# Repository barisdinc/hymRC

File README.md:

Bu projenin amaci role olarak kullanilmak uzere hazirlanan duzeneklerin kontrolunu saglamak ve bu sistemin uzaktan kumandasi ile tanitim bilgilerini olusturacak bir kart tasarimi yapmaktir.

Bu proje **_TA7OM Hudaverdi Gunes_**'in tesviki ile baslatilmistir. Mevcutta yillar once yaptigimiz ve pek cok rolede kullanilan genelde PIC tabanli Role Kontrol kartlarinin daha modern hale getirilmesi hedeflenecektir.

Aklimizdaki ozellikler asagidaki gibidir;

### Temel Ozellikler
1. Islemci unitesi olarak PIC yerine kolay erisilebilir ve programlanabilir ATMEL (Arduino) tercih edilecektir
1. 12 Volt ile beslenecektir
1. Role kontrol ozellikleri olacaktir
1. Durum gosterimi icin LED bulunacaktir
1. Dis arayuz baglantilari optokupler veya roleler uzerinden yapilacaktir
1. COR/CAS destegi olmalidir
1. COR/CAS destegi +/- olabilmelidir
1. Ayarlarin gosterimi icin LCD bulunacaktir (opsiyonel)
1. Ayarlarin goruntulenmesi/degistirilmesi icin rotary encoder bulunacaktir (opsiyonel)
1. Sistem icinde gercek zaman saati bulunacaktir (opsiyonel)
1. Roleye simplex Link sistemi ilave edilebilmelidir
  * Link COR girişi olmalı
  * Ancak Link girişinden sinyal geldiğinde Role de Kuyruk süresi olmamalı
  * İki VHF cihaz ile yapılan Role bir birine UHF üzerinden ücüncü cihaz ile Linkli olsun. 
  * iki cihazdan yapılan VHF Role Normal aktivtesini sürdürürken Kullanıcı Mandalı attığında Role göndermede iken aynı zamanda UHF link cihazı da göndermeye geçmelidir. 
  * Kullanıcı Mandalı bıraktığında Role Kuruk süresi sonrasında kapanacak ancak Link ise hiçbir gecikme olmadan, yani kuyruk süresi olmadan anında kapanacak. Bunun amacı Link üzerinden gelen sinyal zaten bir rokleden gelmekte olup, üzerinde kuyruk süresi vardır. 
  * ikinci bir kuyruk süresine ihtiyaç yoktur.
1. ...

### Role KOntrol Ozellikleri
1. Squelch/Sinyal girisi
1. Otomatik enterferans engelleme
1. ... 

### Uzaktan Kumanda Ozellikleri
1. DTMF ile uzaktan kumanda ozelligi olacaktir
1. Role acma/kapatma
1. Ton acma/kapatma
1. Morse tanitim acma/kapatma
1. AX25 tanitim acma/kapatma
1. belirlenen sure boyunca kapali kalma
1. Otomatik enterferans engelleme acma/kapama
1. Link acma/kapama
1. Kuyruk suresi ayari (uzun/orta/kisa)
1. Fan/Role acma/kapatma
1. AX25 ile uzaktan ayar yuklenmesi yapilabilecektir (opsiyonel)
1. SSTV Goruntusu iste (opsiyonel)
1. ...

### Tanitim Bilgisi
1. Beacon Tanitim ozelligi bulunacaktir (Orn: YM7KO 88.5 KN80WU 5W -10C 138V 121220 1919)
  * Morse olarak istasyon tanitimi basacaktir
  * Morse tanitim icinde asagidaki bilgiler olacaktir
  * Ton bilgisi
  * Lokasyon bilgisi (grid   square)
  * Cikis Gucu
  * Ortam sicakligi
  * Aku voltajlari
  * Tarih ve saat (gercek zamani opsiyonu durumunda
  * ...
  
1. Uzaktan kumanda sifre kontrollu olacaktir
  * Sifre uzaktan degistirilebilecektir
  * Sifre tanimli bir sifre kumesinden (Orn: 10 degisik sifre) sirayla degisecektir, aktif sifre no sorgulanabilecektir
  * ...
  
1. Beacon sinyali AX25 olarak da gonderilecektir
  * AX25 beacon sinyali icinde rolenin tum ayarlarinin aktif durumu bulunabilecektir
  * ...

**NOT:** Liste ilgili goruslerinizi ve eklenmesini istediginiz ozellikleri ISSUE bolumunden veya email ile bize bildiriniz. (barisdinc###gmail.com)

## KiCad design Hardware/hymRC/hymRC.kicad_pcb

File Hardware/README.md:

This folder will contain Schematic and PCB versions for different repeater application options

PCBs arrived...
<IMG SRC=https://github.com/barisdinc/hymRC/blob/main/Hardware/HYMRC_pcb1.jpeg>
<IMG SRC=https://github.com/barisdinc/hymRC/blob/main/Hardware/HYMRC_pcb2.jpeg>

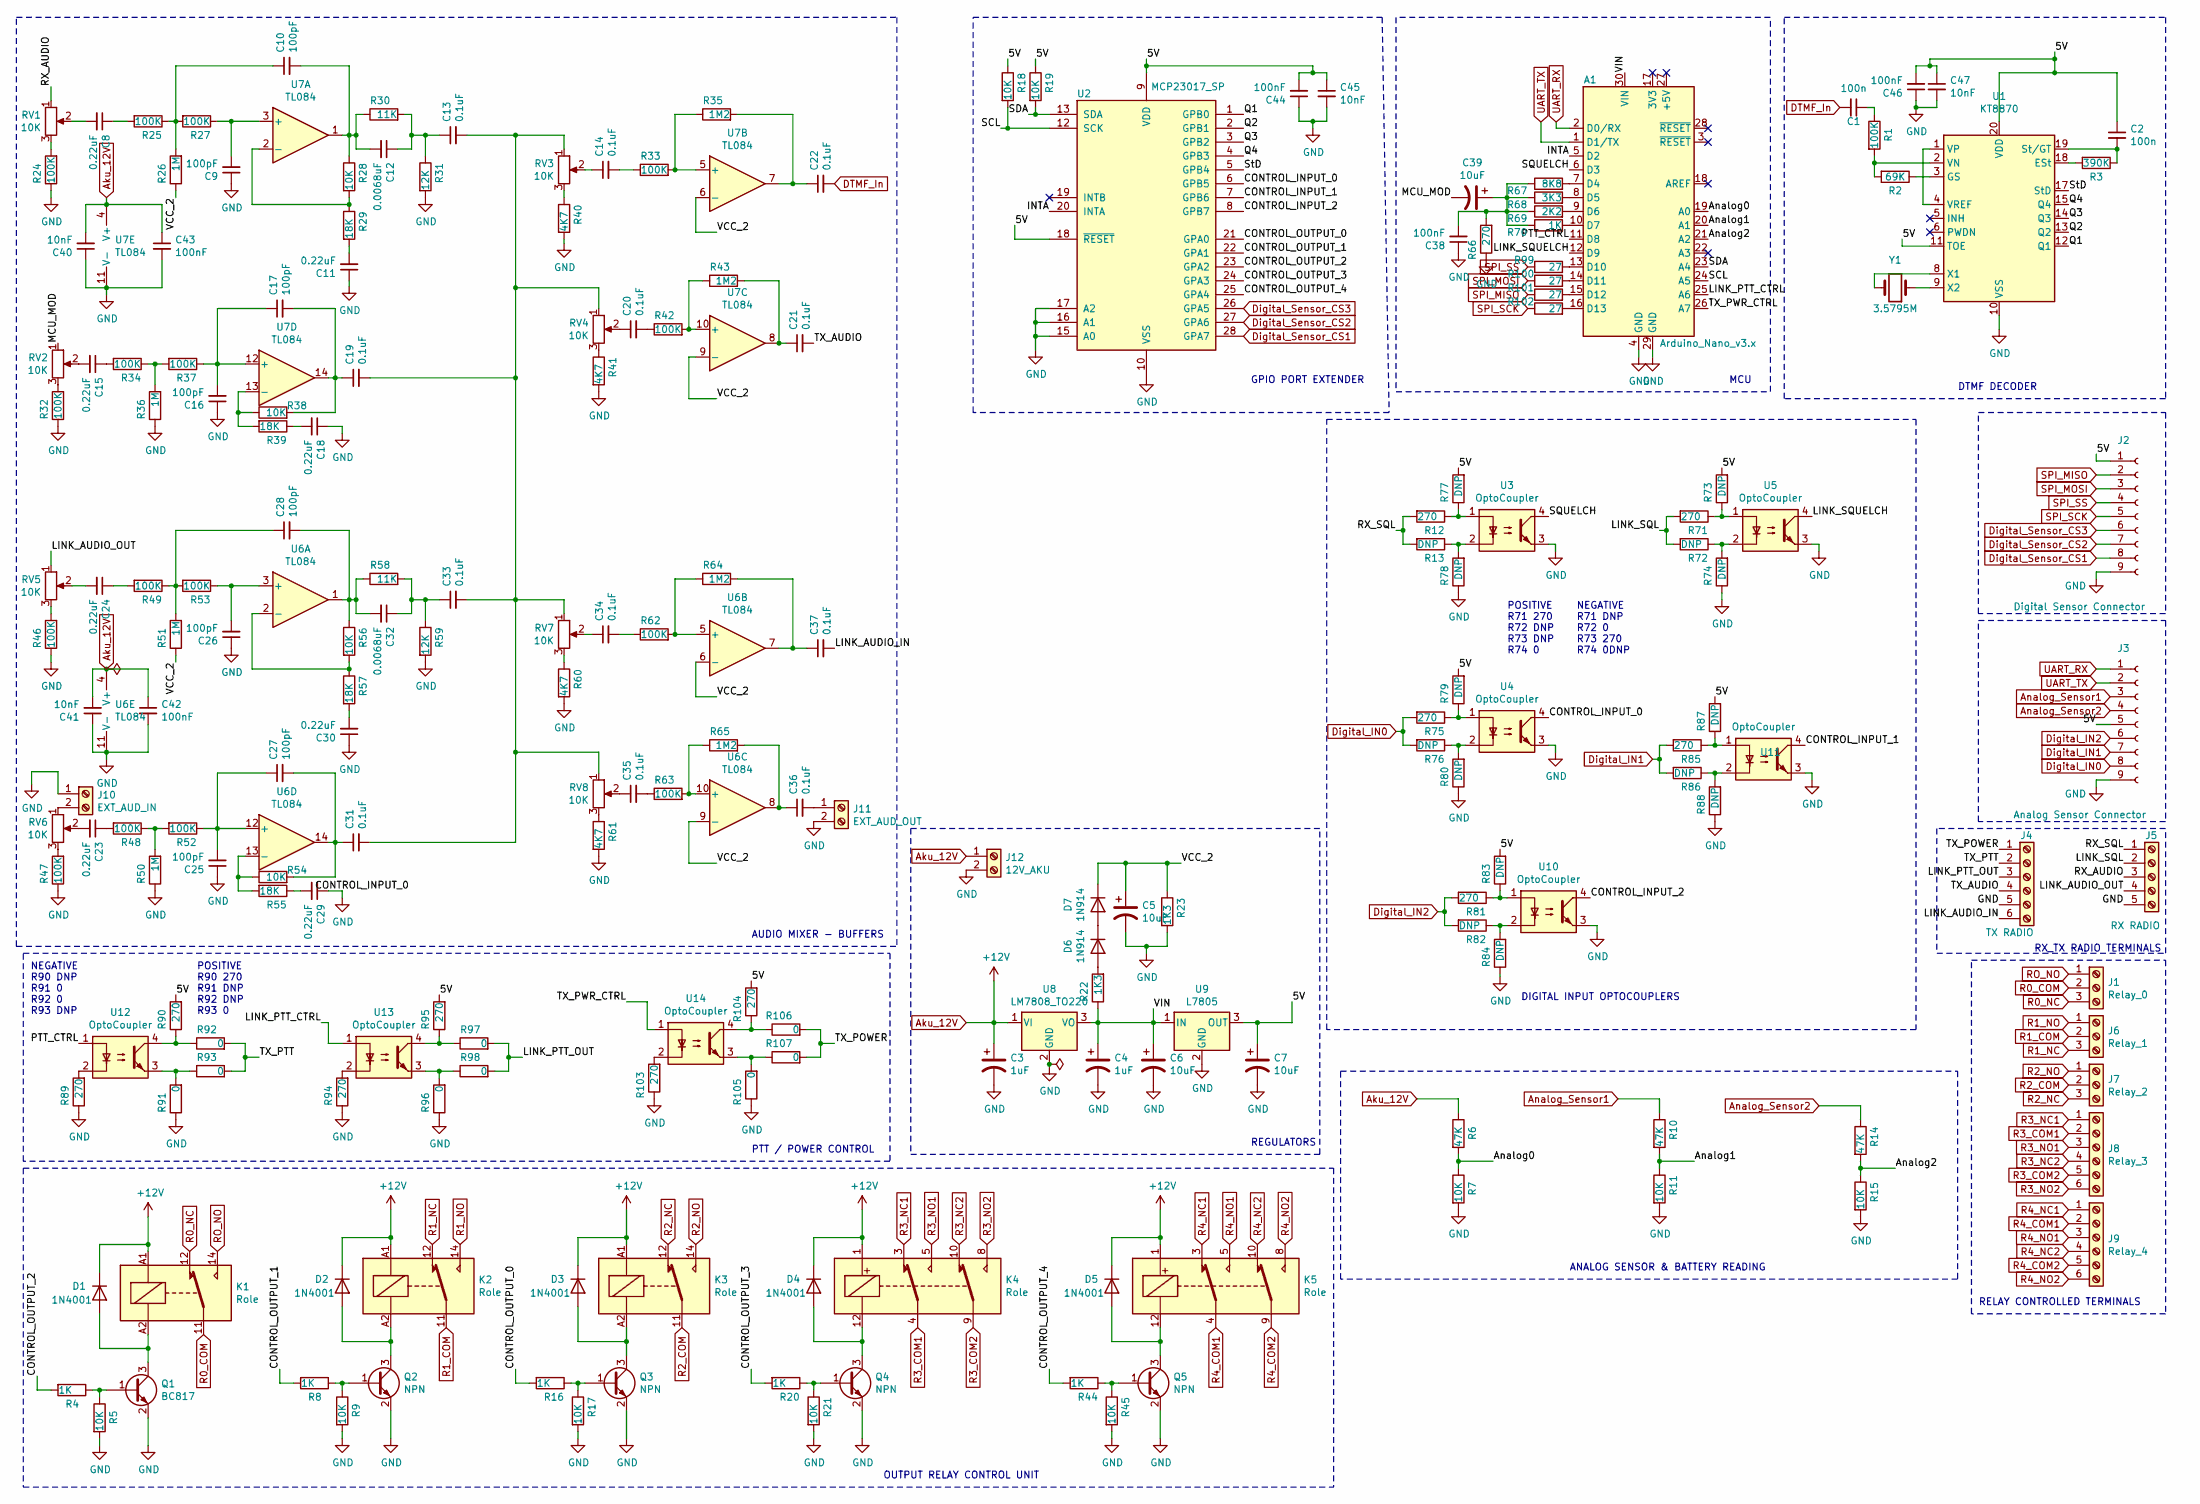
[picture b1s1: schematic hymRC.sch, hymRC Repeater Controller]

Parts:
A1: Arduino_Nano_v3.x; Arduino_Nano
C1, C2: 100n; C_0805_2012Metric_Pad1.18x1.45mm_HandSolder
C3, C4: 1uF; CP_Elec_4x5.8
C5, C6, C7, C39: 10uF; CP_Elec_4x5.8
C8, C11, C15, C18, C23, C24, C29, C30: 0.22uF; C_0805_2012Metric_Pad1.18x1.45mm_HandSolder
C9, C10, C16, C17, C25, C26, C27, C28: 100pF; C_0805_2012Metric_Pad1.18x1.45mm_HandSolder
C12, C32: 0.0068uF; C_0805_2012Metric_Pad1.18x1.45mm_HandSolder
C13, C14, C19, C20, C21, C22, C31, C33, C34, C35, C36, C37: 0.1uF; C_0805_2012Metric_Pad1.18x1.45mm_HandSolder
C38, C42, C43, C44, C46: 100nF; C_0805_2012Metric_Pad1.18x1.45mm_HandSolder
C40, C41, C45, C47: 10nF; C_0805_2012Metric_Pad1.18x1.45mm_HandSolder
D1, D2, D3, D4, D5: 1N4001; D_0805_2012Metric_Pad1.15x1.40mm_HandSolder
D6, D7: 1N914; D_0805_2012Metric_Pad1.15x1.40mm_HandSolder
J1: Relay_0; TerminalBlock_bornier-3_P5.08mm
J2: Digital Sensor Connector; TerminalBlock_4Ucon_1x09_P3.50mm_Horizontal
J3: Analog Sensor Connector; TerminalBlock_4Ucon_1x09_P3.50mm_Horizontal
J4: TX RADIO; TerminalBlock_bornier-6_P5.08mm
J5: RX RADIO; TerminalBlock_bornier-5_P5.08mm
J6: Relay_1; TerminalBlock_bornier-3_P5.08mm
J7: Relay_2; TerminalBlock_bornier-3_P5.08mm
J8: Relay_3; TerminalBlock_bornier-6_P5.08mm
J9: Relay_4; TerminalBlock_bornier-6_P5.08mm
J10: EXT_AUD_IN; TerminalBlock_bornier-2_P5.08mm
J11: EXT_AUD_OUT; TerminalBlock_bornier-2_P5.08mm
J12: 12V_AKU; TerminalBlock_bornier-2_P5.08mm
K1, K2, K3: Role; Relay_SPDT_Finder_34.51_Vertical
K4, K5: Role; Relay_DPDT_Kemet_EE2_NUH
Q1: BC817; SOT-23
Q2, Q3, Q4, Q5: NPN; SOT-23
R1, R24, R25, R27, R32, R33, R34, R37, R42, R46, R47, R48, R49, R52, R53, R62, R63: 100K; R_0805_2012Metric_Pad1.20x1.40mm_HandSolder
R2: 69K; R_0805_2012Metric_Pad1.20x1.40mm_HandSolder
R3: 390K; R_0805_2012Metric_Pad1.20x1.40mm_HandSolder
R4, R8, R16, R20, R44, R70: 1K; R_0805_2012Metric_Pad1.20x1.40mm_HandSolder
R5, R7, R9, R11, R15, R17, R18, R19, R21, R28, R38, R45, R54, R56: 10K; R_0805_2012Metric_Pad1.20x1.40mm_HandSolder
R6, R10, R14: 47K; R_0805_2012Metric_Pad1.20x1.40mm_HandSolder
R12, R66, R71, R75, R81, R85, R89, R90, R94, R95, R103, R104: 270; R_0805_2012Metric_Pad1.20x1.40mm_HandSolder
R13, R72, R73, R74, R76, R77, R78, R79, R80, R82, R83, R84, R86, R87, R88: DNP; R_0805_2012Metric_Pad1.20x1.40mm_HandSolder
R22, R23: 1K3; R_0805_2012Metric_Pad1.20x1.40mm_HandSolder
R26, R36, R50, R51: 1M; R_0805_2012Metric_Pad1.20x1.40mm_HandSolder
R29, R39, R55, R57: 18K; R_0805_2012Metric_Pad1.20x1.40mm_HandSolder
R30, R58: 11K; R_0805_2012Metric_Pad1.20x1.40mm_HandSolder
R31, R59: 12K; R_0805_2012Metric_Pad1.20x1.40mm_HandSolder
R35, R43, R64, R65: 1M2; R_0805_2012Metric_Pad1.20x1.40mm_HandSolder
R40, R41, R60, R61: 4K7; R_0805_2012Metric_Pad1.20x1.40mm_HandSolder
R67: 8K8; R_0805_2012Metric_Pad1.20x1.40mm_HandSolder
R68: 3K3; R_0805_2012Metric_Pad1.20x1.40mm_HandSolder
R69: 2K2; R_0805_2012Metric_Pad1.20x1.40mm_HandSolder
R91, R92, R93, R96, R97, R98, R105, R106, R107: 0; R_0805_2012Metric_Pad1.20x1.40mm_HandSolder
R99, R100, R101, R102: 27; R_0805_2012Metric_Pad1.20x1.40mm_HandSolder
RV1, RV2, RV3, RV4, RV5, RV6, RV7, RV8: 10K; Potentiometer_ACP_CA9-VSMD_Vertical
U1: KT8870; SSOP-20_5.3x7.2mm_P0.65mm
U2: MCP23017_SP; SOIC-28W_7.5x17.9mm_P1.27mm
U3, U4, U5, U10, U11, U12, U13, U14: OptoCoupler; SMDIP-4_W7.62mm
U6, U7: TL084; SOIC-14_3.9x8.7mm_P1.27mm
U8: LM7808_TO220; TO-220-3_Vertical
U9: L7805; TO-220-3_Vertical
Y1: 3.5795M; Crystal_SMD_SeikoEpson_MC405-2Pin_9.6x4.1mm_HandSoldering

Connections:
/5V: C2.1, C7.1, C44.2, C45.1, C46.2, C47.1, J2.1, J3.5, R18.1, R19.1, R73.2, R77.2, R79.2, R83.2, R87.2, R90.2, R95.2, R104.2, U1.11 (TOE), U1.20 (VDD), U2.9 (VDD), U2.18 (~RESET~), U9.3 (OUT)
/Analog0: A1.19 (A0), R6.2, R7.1
/Analog1: A1.20 (A1), R10.2, R11.1
/Analog2: A1.21 (A2), R14.2, R15.1
/CONTROL_INPUT_0: U2.6 (GPB5), U4.4
/CONTROL_INPUT_1: U2.7 (GPB6), U11.4
/CONTROL_INPUT_2: U2.8 (GPB7), U10.4
/CONTROL_OUTPUT_0: R16.2, U2.21 (GPA0)
/CONTROL_OUTPUT_1: R8.2, U2.22 (GPA1)
/CONTROL_OUTPUT_2: R4.2, U2.23 (GPA2)
/CONTROL_OUTPUT_3: R20.2, U2.24 (GPA3)
/CONTROL_OUTPUT_4: R44.2, U2.25 (GPA4)
/INTA: A1.5 (D2), U2.20 (INTA)
/LINK_AUDIO_IN: C37.2, J4.6
/LINK_AUDIO_OUT: J5.4, RV5.1
/LINK_PTT_CTRL: A1.25 (A6), U13.1
/LINK_PTT_OUT: J4.3, R97.2, R98.2
/LINK_SQL: J5.2, R71.2, R72.2
/LINK_SQUELCH: A1.12 (D9), U5.4
/MCU_MOD: C39.2, RV2.1
/PTT_CTRL: A1.11 (D8), U12.1
/Q1: U1.12 (Q1), U2.1 (GPB0)
/Q2: U1.13 (Q2), U2.2 (GPB1)
/Q3: U1.14 (Q3), U2.3 (GPB2)
/Q4: U1.15 (Q4), U2.4 (GPB3)
/RX_AUDIO: J5.3, RV1.1
/RX_SQL: J5.1, R12.2, R13.2
/SCL: A1.24 (A5), R18.2, U2.12 (SCK)
/SDA: A1.23 (A4), R19.2, U2.13 (SDA)
/SQUELCH: A1.6 (D3), U3.4
/StD: U1.17 (StD), U2.5 (GPB4)
/TX_AUDIO: C21.2, J4.4
/TX_POWER: J4.1, R106.2, R107.2
/TX_PTT: J4.2, R92.2, R93.2
/TX_PWR_CTRL: A1.26 (A7), U14.1
/VCC_2: C5.1, D7.1 (K), R23.1, R26.1, R51.1, U6.6 (-), U6.9 (-), U7.6 (-), U7.9 (-)
/VIN: A1.30 (VIN), C4.1, C6.1, R22.1, U8.3 (VO), U9.1 (IN)
Aku_12V: C3.1, C40.2, C41.2, C42.1, C43.1, D1.1 (K), D2.1 (K), D3.1 (K), D4.1 (K), D5.1 (K), J12.1, K1.A1, K2.A1, K3.A1, K4.1, K5.1, R6.1, U6.4 (V+), U7.4 (V+), U8.1 (VI)
Analog_Sensor1: J3.3, R10.1
Analog_Sensor2: J3.4, R14.1
DTMF_In: C1.2, C22.2
Digital_IN0: J3.8, R75.2, R76.2
Digital_IN1: J3.7, R85.2, R86.2
Digital_IN2: J3.6, R81.2, R82.2
Digital_Sensor_CS1: J2.8, U2.28 (GPA7)
Digital_Sensor_CS2: J2.7, U2.27 (GPA6)
Digital_Sensor_CS3: J2.6, U2.26 (GPA5)
GND: A1.4 (GND), A1.29 (GND), C3.2, C4.2, C5.2, C6.2, C7.2, C9.1, C11.1, C16.1, C18.1, C25.1, C26.1, C29.1, C30.1, C38.1, C40.1, C41.1, C42.2, C43.2, C44.1, C45.2, C46.1, C47.2, J2.9, J3.9, J4.5, J5.5, J10.1, J11.2, J12.2, Q1.2 (E), Q2.2 (E), Q3.2 (E), Q4.2 (E), Q5.2 (E), R5.2, R7.2, R9.2, R11.2, R15.2, R17.2, R21.2, R23.2, R24.1, R31.2, R32.1, R36.1, R40.2, R41.2, R45.2, R46.1, R47.1, R50.1, R59.2, R60.2, R61.2, R66.1, R74.1, R78.1, R80.1, R84.1, R88.1, R89.1, R91.1, R94.1, R96.1, R103.1, R105.1, U1.10 (VSS), U2.10 (VSS), U2.15 (A0), U2.16 (A1), U2.17 (A2), U3.3, U4.3, U5.3, U6.11 (V-), U7.11 (V-), U8.2 (GND), U9.2 (GND), U10.3, U11.3
unnamed: A1.7 (D4), R67.2
unnamed: A1.8 (D5), R68.2
unnamed: A1.9 (D6), R69.2
unnamed: A1.10 (D7), R70.2
unnamed: A1.13 (D10), R99.2
unnamed: A1.14 (D11), R100.2
unnamed: A1.15 (D12), R101.2
unnamed: A1.16 (D13), R102.2
unnamed: C1.1, R1.1
unnamed: C2.2, R3.1, U1.19 (St/GT)
unnamed: C8.1, R25.2
unnamed: C8.2, RV1.2
unnamed: C9.2, R27.1, U7.3 (+)
unnamed: C10.1, R25.1, R26.2, R27.2
unnamed: C10.2, C12.2, R28.1, R30.1, U7.1
unnamed: C11.2, R29.2
unnamed: C12.1, C13.1, R30.2, R31.1
unnamed: C13.2, C19.2, C31.2, C33.2, RV3.1, RV4.1, RV7.1, RV8.1
unnamed: C14.1, RV3.2
unnamed: C14.2, R33.1
unnamed: C15.1, R34.2
unnamed: C15.2, RV2.2
unnamed: C16.2, C17.1, R37.1, U7.12 (+)
unnamed: C17.2, C19.1, R38.2, U7.14
unnamed: C18.2, R39.1
unnamed: C20.1, RV4.2
unnamed: C20.2, R42.1
unnamed: C21.1, R43.2, U7.8
unnamed: C22.1, R35.2, U7.7
unnamed: C23.1, R48.2
unnamed: C23.2, RV6.2
unnamed: C24.1, R49.2
unnamed: C24.2, RV5.2
unnamed: C25.2, C27.1, R52.1, U6.12 (+)
unnamed: C26.2, R53.1, U6.3 (+)
unnamed: C27.2, C31.1, R54.2, U6.14
unnamed: C28.1, R49.1, R51.2, R53.2
unnamed: C28.2, C32.2, R56.1, R58.1, U6.1
unnamed: C29.2, R55.1
unnamed: C30.2, R57.2
unnamed: C32.1, C33.1, R58.2, R59.1
unnamed: C34.1, RV7.2
unnamed: C34.2, R62.1
unnamed: C35.1, RV8.2
unnamed: C35.2, R63.1
unnamed: C36.1, R65.2, U6.8
unnamed: C36.2, J11.1
unnamed: C37.1, R64.2, U6.7
unnamed: C38.2, C39.1, R66.2, R67.1, R68.1, R69.1, R70.1
unnamed: D1.2 (A), K1.A2, Q1.3 (C)
unnamed: D2.2 (A), K2.A2, Q2.3 (C)
unnamed: D3.2 (A), K3.A2, Q3.3 (C)
unnamed: D4.2 (A), K4.12, Q4.3 (C)
unnamed: D5.2 (A), K5.12, Q5.3 (C)
unnamed: D6.1 (K), D7.2 (A)
unnamed: D6.2 (A), R22.2
unnamed: J10.2, RV6.1
unnamed: Q1.1 (B), R4.1, R5.1
unnamed: Q2.1 (B), R8.1, R9.1
unnamed: Q3.1 (B), R16.1, R17.1
unnamed: Q4.1 (B), R20.1, R21.1
unnamed: Q5.1 (B), R44.1, R45.1
unnamed: R1.2, R2.2, U1.2 (VN)
unnamed: R2.1, U1.3 (GS)
unnamed: R3.2, U1.18 (ESt)
unnamed: R12.1, R77.1, U3.1
unnamed: R13.1, R78.2, U3.2
unnamed: R24.2, RV1.3
unnamed: R28.2, R29.1, U7.2 (-)
unnamed: R32.2, RV2.3
unnamed: R33.2, R35.1, U7.5 (+)
unnamed: R34.1, R36.2, R37.2
unnamed: R38.1, R39.2, U7.13 (-)
unnamed: R40.1, RV3.3
unnamed: R41.1, RV4.3
unnamed: R42.2, R43.1, U7.10 (+)
unnamed: R46.2, RV5.3
unnamed: R47.2, RV6.3
unnamed: R48.1, R50.2, R52.2
unnamed: R54.1, R55.2, U6.13 (-)
unnamed: R56.2, R57.1, U6.2 (-)
unnamed: R60.1, RV7.3
unnamed: R61.1, RV8.3
unnamed: R62.2, R64.1, U6.5 (+)
unnamed: R63.2, R65.1, U6.10 (+)
unnamed: R71.1, R73.1, U5.1
unnamed: R72.1, R74.2, U5.2
unnamed: R75.1, R79.1, U4.1
unnamed: R76.1, R80.2, U4.2
unnamed: R81.1, R83.1, U10.1
unnamed: R82.1, R84.2, U10.2
unnamed: R85.1, R87.1, U11.1
unnamed: R86.1, R88.2, U11.2
unnamed: R89.2, U12.2
unnamed: R90.1, R92.1, U12.4
unnamed: R91.2, R93.1, U12.3
unnamed: R94.2, U13.2
unnamed: R95.1, R97.1, U13.4
unnamed: R96.2, R98.1, U13.3
unnamed: R103.2, U14.2
unnamed: R104.1, R106.1, U14.4
unnamed: R105.2, R107.1, U14.3
unnamed: U1.1 (VP), U1.4 (VREF)
unnamed: U1.8 (X1), Y1.2
unnamed: U1.9 (X2), Y1.1
R0_COM: J1.2, K1.8, K1.11
R0_NC: J1.3, K1.12
R1_COM: J6.2, K2.8, K2.11
R1_NC: J6.3, K2.12
R1_NO: J6.1, K2.14
R2_COM: J7.2, K3.8, K3.11
R2_NC: J7.3, K3.12
R2_NO: J7.1, K3.14
R3_COM1: J8.2, K4.4
R3_COM2: J8.5, K4.9
R3_NC1: J8.1, K4.3
R3_NC2: J8.4, K4.10
R3_NO1: J8.3, K4.5
R3_NO2: J8.6, K4.8
R4_COM1: J9.2, K5.4
R4_COM2: J9.5, K5.9
R4_NC1: J9.1, K5.3
R4_NC2: J9.4, K5.10
R4_NO1: J9.3, K5.5
R4_NO2: J9.6, K5.8
RO_NO: J1.1, K1.14
SPI_MISO: J2.2, R101.1
SPI_MOSI: J2.3, R100.1
SPI_SCK: J2.5, R102.1
SPI_SS: J2.4, R99.1
UART_RX: A1.2 (D0/RX), J3.1
UART_TX: A1.1 (D1/TX), J3.2

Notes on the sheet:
DTMF DECODER
GPIO PORT EXTENDER
MCU
RELAY CONTROLLED TERMINALS
ANALOG SENSOR & BATTERY READING
REGULATORS
RX_TX RADIO TERMINALS
OUTPUT RELAY CONTROL UNIT
DIGITAL INPUT OPTOCOUPLERS
POSITIVE R71 270 R72 DNP R73 DNP R74 0
NEGATIVE R71 DNP R72 0 R73 270 R74 0DNP
AUDIO MIXER - BUFFERS
NEGATIVE R90 DNP R91 0 R92 0 R93 DNP
POSITIVE R90 270 R91 DNP R92 DNP R93 0
PTT / POWER CONTROL

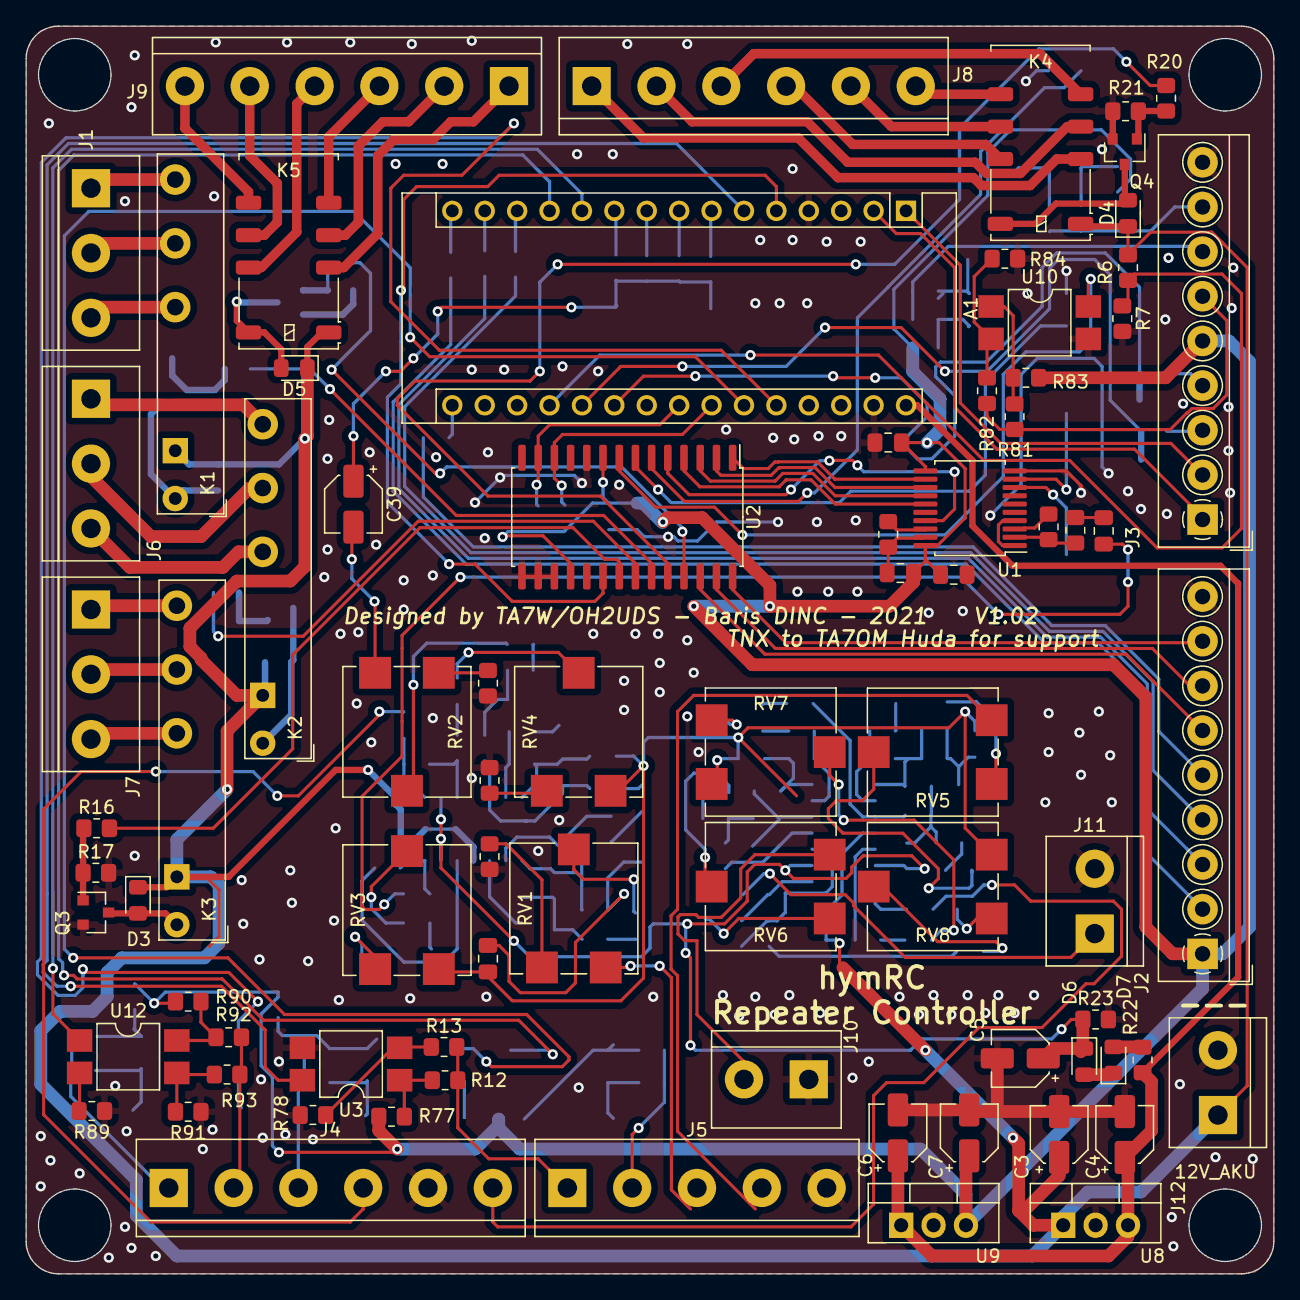
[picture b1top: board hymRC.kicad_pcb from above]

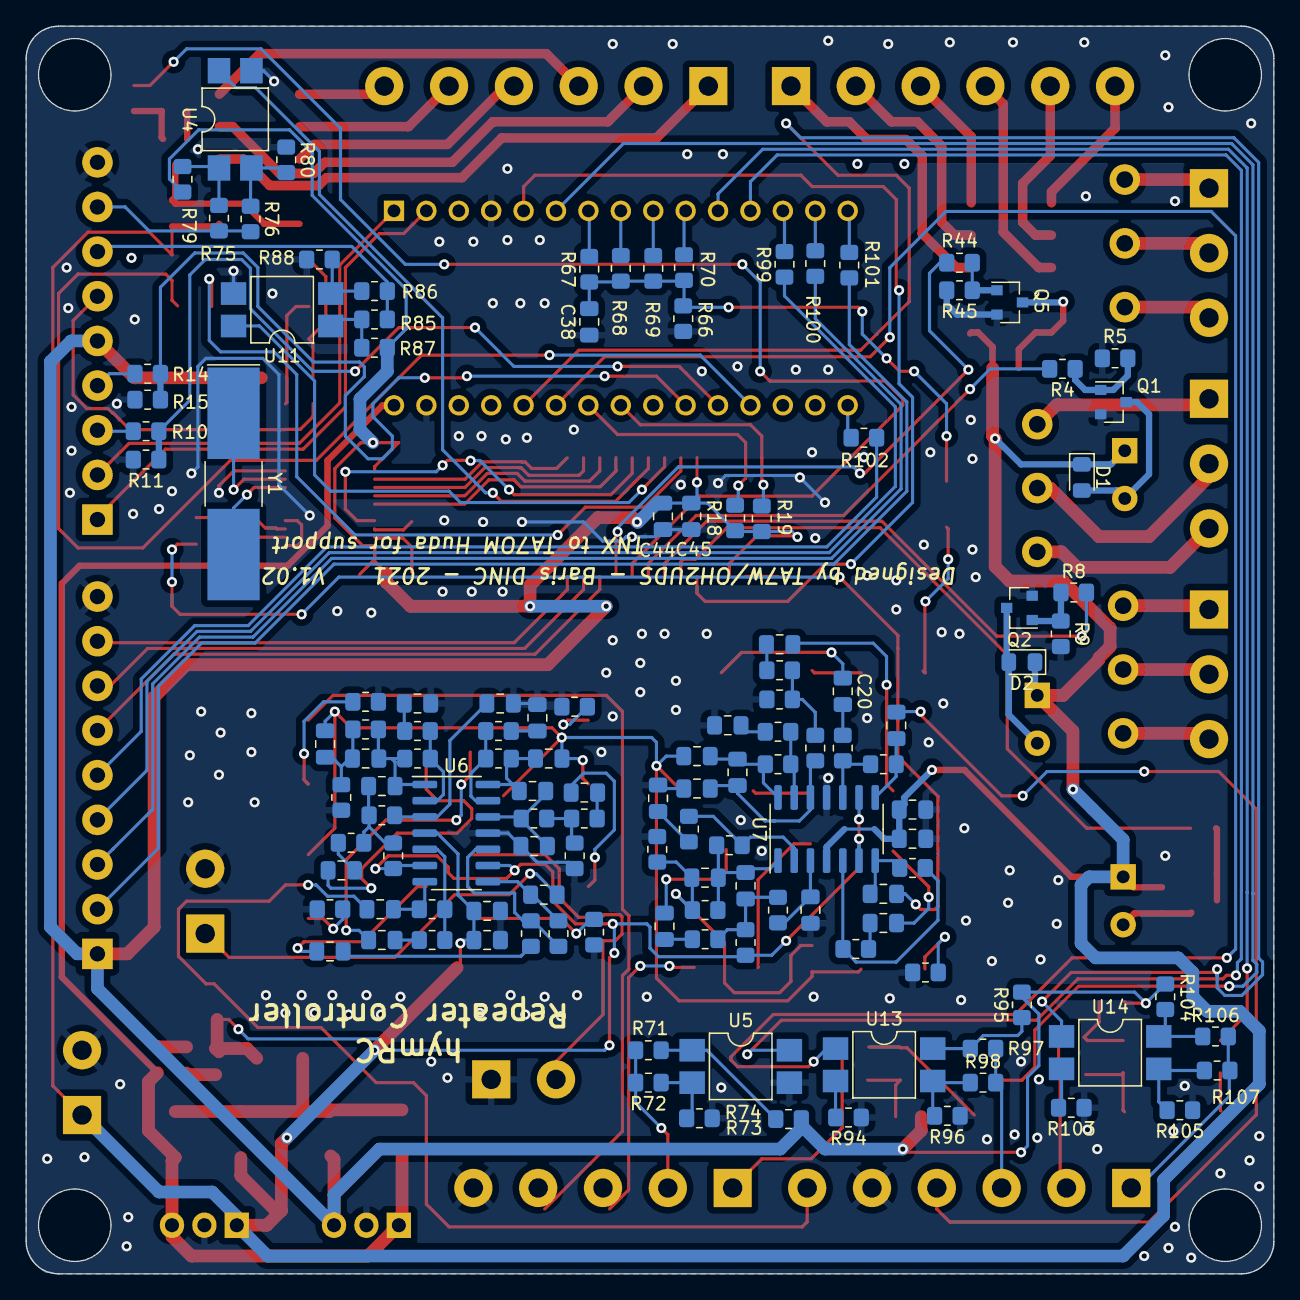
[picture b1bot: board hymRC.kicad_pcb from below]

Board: 2 copper layers, 97.8 x 97.8 mm, 207 parts (129 on the bottom side), 180 nets.

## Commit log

2020-12-30 ilk gereksinimler
2020-12-30 gereksinimlere deva,
2021-01-28 ilk pin atamalari
2021-01-28 pin atamalari
2021-01-28 pin tanimlari
2021-01-28 baglanti pinleri
2021-02-06 KT3170
    I used KT3170 in my experiments
2021-02-06 MT8870
    MT8870 is same as KT3170...
    Mine was MT3170D..... Which is not 18 pin, but 20 pin SOIC.,,,
    Which has slight different pinout which you can find in MT8870D datasheet
2021-02-06 Initial test setup
    My initial workbench setup
2021-02-06 pin corrections
2021-02-06 initial test setup
2021-02-06 3170 Pin secenekleri
2021-02-06 Ornek Uygulama
2021-02-06 uygulama
2021-02-06 Sample project added
2021-02-06 initial software
2021-02-06 initial startup
2021-02-06 txdelay and tail
2021-02-07 SQL -> TX OK
2021-02-07 remote commands OK
2021-02-07 PTT Kontrol
2021-02-20 port extender
2021-02-21 MCP23017 added
2021-02-21 Draft Schematic
2021-02-21 readme added
2021-03-13 huda calisma
2021-03-17 audio buffers added
2021-03-17 opkuplers added.. both negative and positive triggered
2021-03-18 main component footprints and links added to library
2021-03-18 resistors changed to smd 0805
2021-03-18 test
2021-03-18 capcsitors are 0805 now
2021-03-18 DRC checks resolved
2021-03-18 initial PCB
2021-04-04 Audio section completed
2021-04-04 Set theme jekyll-theme-time-machine
2021-04-05 all connected somehow
2021-04-05 digitals connected
2021-04-05 routing finished
2021-04-05 3d finished
2021-04-05 3d wrl added
2021-04-05 all done
2021-04-05 BOM list
2021-04-05 Titles added
2021-04-05 titles added to PCBs
2021-04-06 SOIC-20 footprint squeezed
2021-05-10 PCBs arrived
2025-09-29 guncellemeler suruyor...
